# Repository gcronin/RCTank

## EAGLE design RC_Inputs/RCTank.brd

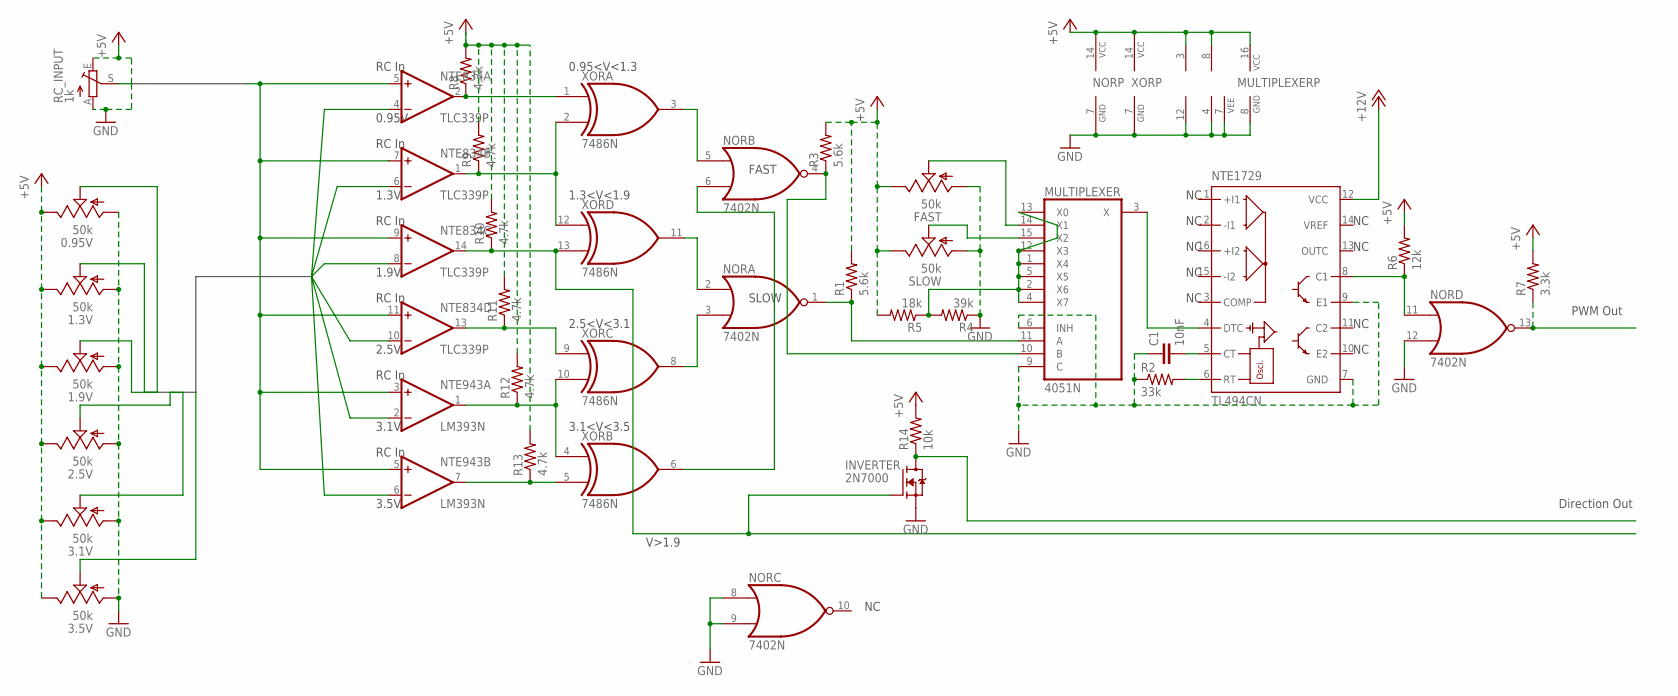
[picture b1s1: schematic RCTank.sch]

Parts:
0.95V, 1.3V, 1.9V, 2.5V, 3.1V, 3.5V: 50k; S64W
C1: 10nF; C2.5-5
FAST: 50k; S64W
INVERTER: 2N7000; TO92-
MULTIPLEXER: 4051N; DIL16
NOR: 7402N; DIL14
NTE834: TLC339P; DIL14
NTE943: LM393N; DIL08
NTE1729: TL494CN; DIL16
R1, R3: 5.6k; 0204/7
R2: 33k; 0204/7
R4: 39k; 0204/7
R5: 18k; 0204/7
R6: 12k; 0204/7
R7: 3.3k; 0204/7
R8, R9, R10, R11, R12, R13: 4.7k; 0204/7
R14: 10k; 0204/7
RC_INPUT: 1k; B25V
SLOW: 50k; S64W
XOR: 7486N; DIL14

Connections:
0.95V: 0.95V.S, NTE834.4 (-IN)
1.3V: 1.3V.S, NTE834.6 (-IN)
1.9V: 1.9V.S, NTE834.8 (-IN)
2.5V: 2.5V.S, NTE834.10 (-IN)
3.1V: 3.1V.S, NTE943.2 (-IN)
3.5V: 3.5V.S, NTE943.6 (-IN)
+5V: 0.95V.E, 1.3V.E, 1.9V.E, 2.5V.E, 3.1V.E, 3.5V.E, FAST.E, MULTIPLEXER.16 (VCC), NOR.14 (VCC), NTE834.3 (V+), NTE943.8 (V+), R1.2, R3.2, R5.2, R6.2, R7.2, R8.2, R9.2, R10.2, R11.2, R12.2, R13.2, R14.2, RC_INPUT.E, SLOW.E, XOR.14 (VCC)
+12V: NTE1729.12 (VCC)
GND: 0.95V.A, 1.3V.A, 1.9V.A, 2.5V.A, 3.1V.A, 3.5V.A, C1.1, FAST.A, INVERTER.3 (S), MULTIPLEXER.6 (INH), MULTIPLEXER.7 (VEE), MULTIPLEXER.8 (GND), MULTIPLEXER.9 (C), NOR.7 (GND), NOR.8 (I0), NOR.9 (I1), NOR.12 (I1), NTE834.12 (V-), NTE943.4 (V-), NTE1729.7 (GND), NTE1729.9 (E1), R2.1, R4.1, RC_INPUT.A, SLOW.A, XOR.7 (GND)
unnamed: NOR.11 (I0), NTE1729.8 (C1), R6.1
unnamed: NOR.13 (O), R7.1
unnamed: MULTIPLEXER.10 (B), NOR.4 (O), R3.1
unnamed: INVERTER.1 (D), R14.1
unnamed: FAST.S, MULTIPLEXER.14 (X1)
unnamed: MULTIPLEXER.15 (X2), SLOW.S
unnamed: NOR.5 (I0), XOR.3 (O)
unnamed: NOR.2 (I0), XOR.11 (O)
unnamed: NTE834.2 (OUT), R8.1, XOR.1 (I0)
unnamed: NTE834.1 (OUT), R9.1, XOR.2 (I1), XOR.12 (I0)
unnamed: MULTIPLEXER.1 (X4), MULTIPLEXER.2 (X6), MULTIPLEXER.4 (X7), MULTIPLEXER.5 (X5), MULTIPLEXER.12 (X3), MULTIPLEXER.13 (X0), R4.2, R5.1
unnamed: NTE834.13 (OUT), R11.1, XOR.9 (I0)
unnamed: NTE943.1 (OUT), R12.1, XOR.4 (I0), XOR.10 (I1)
unnamed: NTE943.7 (OUT), R13.1, XOR.5 (I1)
unnamed: NOR.3 (I1), XOR.8 (O)
unnamed: INVERTER.2 (G), NTE834.14 (OUT), R10.1, XOR.13 (I1)
unnamed: MULTIPLEXER.11 (A), NOR.1 (O), R1.1
unnamed: NOR.6 (I1), XOR.6 (O)
unnamed: C1.2, NTE1729.5 (CT)
unnamed: NTE1729.6 (RT), R2.2
unnamed: MULTIPLEXER.3 (X), NTE1729.4 (DTC)
SIG: NTE834.5 (+IN), NTE834.7 (+IN), NTE834.9 (+IN), NTE834.11 (+IN), NTE943.3 (+IN), NTE943.5 (+IN), RC_INPUT.S

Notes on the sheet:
0.95<V<1.3
1.3<V<1.9
2.5<V<3.1
3.1<V<3.5
RC In
0.95V
1.3V
1.9V
2.5V
3.1V
3.5V
PWM Out
Direction Out
V>1.9
FAST
SLOW

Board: 2 copper layers, 31 parts (0 on the bottom side), 30 nets, no tracks yet.

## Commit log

2022-03-14 Initial Commit
    RC controlled tank with laser on 2-axis turret. Description and Eagle PCB files.
